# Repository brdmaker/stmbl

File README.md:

CI (`.github/workflows/ci.yml`): the host simulator's `make -C host check` and the firmware build (`make deploy`, vibsensor, brdstepper; the images are kept as artifacts) on every push and pull request.

DISCLAIMER
===

THE AUTHORS OF THIS SOFTWARE ACCEPT ABSOLUTELY NO LIABILITY FOR
ANY HARM OR LOSS RESULTING FROM ITS USE.  IT IS _EXTREMELY_ UNWISE
TO RELY ON SOFTWARE ALONE FOR SAFETY.  Any machinery capable of
harming persons must have provisions for completely removing power
from all motors, etc, before persons enter any danger area.  All
machinery must be designed to comply with local and national safety
codes, and the authors of this software can not, and do not, take
any responsibility for such compliance.

This software is released under the GPLv3.

STMBL
=====
There is work in progress on documentation: https://github.com/rene-dev/stmbl/blob/master/docs/src/Getting%20Started.adoc

**IRC: #stmbl on irc.hackint.eu**
https://webirc.hackint.org/#stmbl

STMBL is an open source servo drive designed for Retrofitting CNC machines and Robots. It supports Industrial AC and DC servos with up to 320V and 2kW (see [specs](https://github.com/rene-dev/stmbl/wiki/specs) for details).

Documentation about the PCB and pinout of the feedback connector:

https://github.com/rene-dev/stmbl/wiki/Pinouts

https://github.com/rene-dev/stmbl/wiki/PCB

##### Hardware version 4.1

##### Driving a Bosch Turboscara
https://www.youtube.com/watch?v=d6NH1W7DUnQ  
https://www.youtube.com/watch?v=oTllxnYAgFc

##### Driving a Manutec Robot
https://www.youtube.com/watch?v=gwgnAeGjZrA  
https://www.youtube.com/watch?v=wXLcAZwjlzE

##### Driving a Weeke BP12 VMC
https://www.youtube.com/watch?v=24LftGNp4MI

##### Driving a Haas VF0 (Spindle + Axes)
https://www.youtube.com/watch?v=kqenepupJIs

##### Drivetest
https://www.youtube.com/watch?v=-E1o_5cFyto

#### Supported Motors
* Synchronous AC Servos
* Asynchronous AC Servos
* DC Servos
* 2 Phase HF spindle motors

#### Supported Feedback systems
* Resolvers
* Incremental encoders
* sin/cos encoder interpolation
* Mitsubishi absolute encoders
* Sanyo Denki absolute encoders
* Yaskawa absolute encoders
* Sick HIPERFACE®
* Tamagawa SmartAbs

##### Planned:
* EnDat
* BiSS
* SSI
* Sanyo Denki wire-saving incremental encoder

#### Supported Position/Velocity Commands Inputs:
* Smartserial
* Quadrature
* Step/direction
* RS485

#### TODO
* Sensorless FOC

#### Directories
* [hw/spice/](hw/spice/) Spice simulation for resolver interface
* [hw/kicad/v4.0/](hw/kicad/v4.0/) kicad files for version 4
* [src/](src/) STM32F4 code, command, feedback and control loop
* [stm32f303/](stm32f303/) STM32F3 code, running on the HV side, generating PWM

##### Commercial Applications

Should you find the GPL license insufficient for your needs, other licenses
can be purchased from my company.

Likewise, please contact us should you wish to fund the further development
of this project, or are interesed in custom hardware, software, or commercial support.

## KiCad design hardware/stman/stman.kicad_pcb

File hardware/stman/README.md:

# stman KiCad project

The schematic of **stman**, the stmbl with an analog output
([docs/stman.md](../../docs/stman.md)). It is stmbl v4.0's LV board
(`hw/kicad/v4.0`) with the stman changes, as a KiCad 7 project. The
schematic is in [doc/stman-schematic.pdf](doc/stman-schematic.pdf).

**stmbl's sheets keep their drawing.** KiCad 7 can't read the KiCad 5
sheets, so `gen/build.py` converts them with `hardware/kigen/legacy.py`.
Every symbol, wire, junction, label and note stays where stmbl has it. Then
it edits them in place.

| sheet | what |
|---|---|
| `stman.kicad_sch` | root, stmbl's `ctrl.sch`: P14 (the HV board link) removed; the new sheets added |
| `supply.kicad_sch` | stmbl's: P3 24 V in (+UI / 0VI), D200 reverse polarity in the wire up from P3, bucks 5 V / 12 V / port 5 V now LMR51420YF (ACT4088 is EOL; stmbl's drawing, pins renumbered, dividers for VFB 0.6 V, EN R212-R214, D9/D12/D13 not fitted, input caps 4.7 µF 50 V; see docs/stman.md, *Power tree*), LDO 3.3 V |
| `f4.kicad_sch` | stmbl's MCU sheet. U22 (ESD on the CMD lines) removed. The MCU pins stman uses carry their new nets as global labels where stmbl's labels were, or at the pin when it was tied to something else (`build.MCU`) |
| `cmd.kicad_sch` | stmbl's CMD port, isolated. U8/U9 stay on the cable side (SS_5V, SS_GND, SS_SHIELD); U10, U11 and their parts are removed; U200 ISO7331FC joins them to the MCU; JP200/JP201 pick the cable's +5 V and GND pairs |
| `fb.kicad_sch` (FB0, FB1) | stmbl's, with a polyfuse (F200 / F201) between the port supply and the connector's pin 7 |
| `io.kicad_sch` | stmbl's IO sheet with the outputs, analog inputs, fan and 2x6 header removed; the status LEDs kept |
| `dac.kicad_sch` | new: AD5761R ×2, OPA2197 Sallen-Key low-pass, TVS, J5; NMA1215 ±15 V |
| `ain.kicad_sch` | new: AD7606 monitor ADC, input resistors, rail dividers, J6 |
| `drvio.kicad_sch` | new: ITS724G ×2 (OUT1-8, J7), 8 inputs (J8), MAX6369 watchdog and the 74LVC2G08 gate on OUT1/OUT2 |

The new sheets are drawn the way `hardware/kigen` draws: parts in framed
groups, each pin joined to its net by a label. Global labels connect them
to the MCU sheet.

Refs from 200 up are stman's. The others are stmbl v4.0's, with the same
values and footprints (stmbl's footprint library, `fp-lib-table` ->
`hw/kicad/lib/stmbl.pretty`).

## The board

`stman.kicad_pcb` comes from `gen/pcb.py`. It is placed, not routed; see
docs/stman.md, *The board*.
- **Outline:** stmbl v4.0's (the v4 case fits), with the HV/LV slots
  removed.
- **stmbl's parts:** each is stmbl's footprint, copied from
  `hw/kicad/v4.0/stmbl_4.0.kicad_pcb` where stmbl placed it.
- **New parts:** the connectors and main ICs at fixed positions (`FIXED`,
  `FLUSH`); their passives beside the parts they connect to.
- **Isolation barrier:** a copper-free rule area for the smart-serial cable
  side.
- **Ground plane:** on In1, not filled.

`gen/pcb.py` prints the courtyard overlaps that involve new parts (none),
and how many stmbl v4.0 has among its own parts (20, unchanged).

## Make

| target | does |
|---|---|
| `make sch` | `gen/build.py`: convert, edit, add the new sheets |
| `make check` | `gen/check.py`: the netlist kicad-cli exports against two references (below) |
| `make pcb` | `gen/pcb.py`: the board (placement redone; hand edits to it are lost) |
| `make doc` | the PDF and the placement renders |

`gen/check.py` checks:
- **stmbl's own nets:** every net of stmbl's 2018 netlist
  (`hw/kicad/v4.0/stmbl_4.0.net`) among the parts kept is still one net,
  except the ones stman changes on purpose;
- **stman's nets:** every pin of the new parts, the MCU pins and the
  isolator is on the net the design gives it, and no two of those nets are
  joined.

At the time of writing it reports 229 nets, 338 parts, OK.

Edit the generator (`gen/build.py`, `gen/newsheets.py`) rather than the
sheets while the design is moving. Once layout starts, edit in KiCad.

## To check before layout (✱)

- **AD5761R:** the pin numbers (its symbol is drawn from the datasheet's pin
  names).
- **AD7606:** in serial mode, check that DOUT_A is tri-stated with /CS high
  (it shares MISO with the DACs).
- **MAX6369:** the SET0-2 timeout table.
- **ITS724G:** the status logic.
- **Mesa's smart-serial RJ45 pinout:** which pairs carry +5 V and GND
  (JP200/JP201).

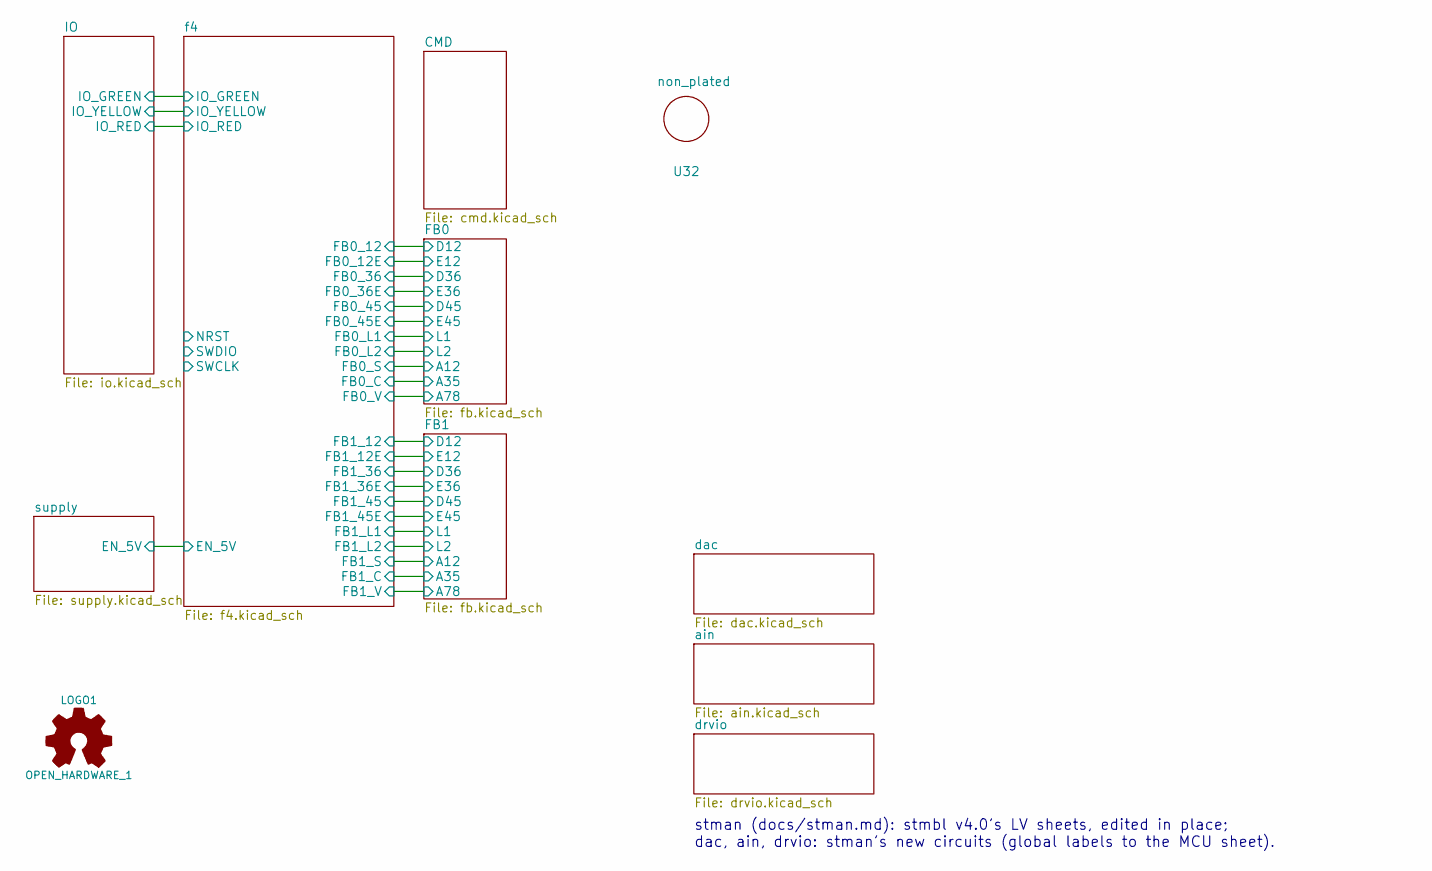
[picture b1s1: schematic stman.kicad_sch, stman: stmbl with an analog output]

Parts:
LOGO1: OPEN_HARDWARE_1; Symbol_OSHW-Logo_SilkScreen
U32: non_plated; non_plated_3mm

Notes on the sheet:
stman (docs/stman.md): stmbl v4.0's LV sheets, edited in place; dac, ain, drvio: stman's new circuits (global labels to the MCU sheet).

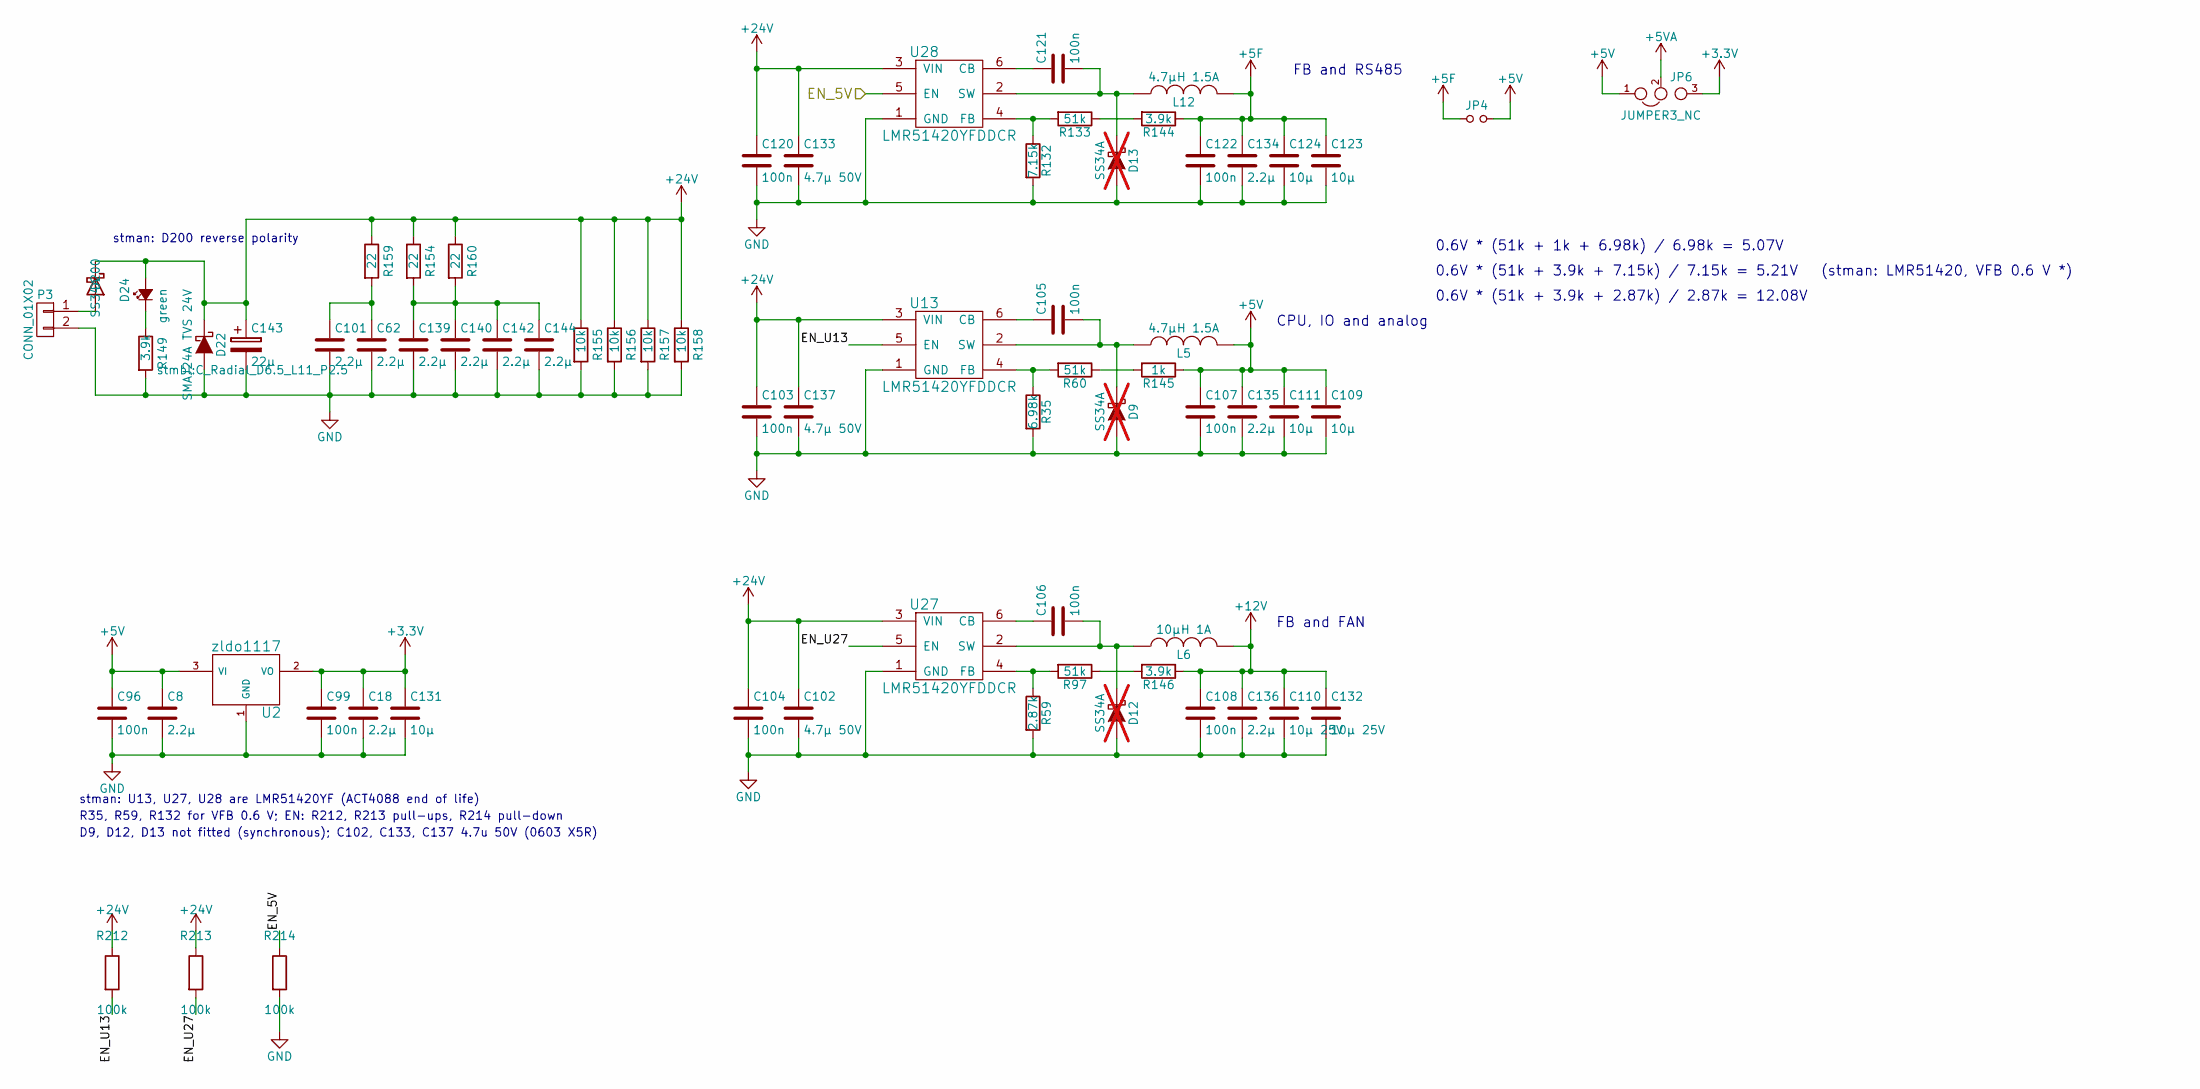
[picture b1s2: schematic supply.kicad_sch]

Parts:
C8, C18, C62, C101, C134, C135, C136, C139, C140, C142, C144: 2.2µ; C_0603; Voltage 35V; Tolerance X5R
C96, C99, C103, C104, C105, C106, C107, C108, C120, C121, C122: 100n; C_0603; Voltage 50V; Tolerance X5R
C102, C133, C137: 4.7µ 50V; C_0603; Voltage 35V; Tolerance X5R
C109, C111, C123, C124, C131: 10µ; C_0805; Voltage 25V; Tolerance X5R
C110, C132: 10µ 25V; C_0805; Voltage 25V; Tolerance X5R
C143: 22µ; C_Radial_D6.5_L11_P2.5; Voltage 50V
D9, D12, D13: SS34A; SMA_Standard; not fitted
D22: SMAJ24A TVS 24V; SMA_Standard
D24: green; LED-0805-SIDE
D200: SS34A; SMA_Standard
JP4: Jumper_NO_Small; SOLDER_JUMPER
JP6: JUMPER3_NC; SOLDER_JUMPER_3_NC
L5, L12: 4.7µH 1.5A; SMD_INDUCTOR_32x25
L6: 10µH 1A; SMD_INDUCTOR_32x25
P3: CONN_01X02; RM3.5_1x2
R35: 6.98k; R_0603; Tolerance 1%
R59: 2.87k; R_0603; Tolerance 1%
R60, R97, R133: 51k; R_0603; Tolerance 1%
R132: 7.15k; R_0603; Tolerance 1%
R144, R146, R149: 3.9k; R_0603; Tolerance 1%
R145: 1k; R_0603; Tolerance 1%
R154, R159, R160: 22; R_0603; Tolerance 1%
R155, R156, R157, R158: 10k; R_0603; Tolerance 1%
R212, R213, R214: 100k; R_0603
U2: zldo1117; SOT-223
U13, U27, U28: LMR51420YFDDCR; SOT-23-6

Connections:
+5F: C122.1, C123.1, C124.1, C134.1, JP4.1, L12.2, R144.1; also elsewhere on the board
+5V: C8.1, C96.1, C107.1, C109.1, C111.1, C135.1, JP4.2, JP6.1, L5.2, R145.1, U2.3 (VI); also elsewhere on the board
+5VA: JP6.2; also elsewhere on the board
+12V: C108.1, C110.1, C132.1, C136.1, L6.2, R146.1; also elsewhere on the board
+24V: C102.1, C103.1, C104.1, C120.1, C133.1, C137.1, C143.1, D22.1 (K), D24.2 (A), D200.1 (K), R154.1, R155.1, R156.1, R157.1, R158.1, R159.1, R160.1, R212.1, R213.1, U13.3 (VIN), U27.3 (VIN), U28.3 (VIN); also elsewhere on the board
/supply/EN_5V: R214.1, U28.5 (EN); also elsewhere on the board
/supply/EN_U13: R212.2, U13.5 (EN)
/supply/EN_U27: R213.2, U27.5 (EN)
GND: C8.2, C18.2, C62.2, C96.2, C99.2, C101.2, C102.2, C103.2, C104.2, C107.2, C108.2, C109.2, C110.2, C111.2, C120.2, C122.2, C123.2, C124.2, C131.2, C132.2, C133.2, C134.2, C135.2, C136.2, C137.2, C139.2, C140.2, C142.2, C143.2, C144.2, D9.2 (A), D12.2 (A), D13.2 (A), D22.2 (A), P3.2, R35.2, R59.2, R132.2, R149.2, R155.2, R156.2, R157.2, R158.2, R214.2, U2.1 (GND), U13.1 (GND), U27.1 (GND), U28.1 (GND); also elsewhere on the board
unnamed: C62.1, C101.1, R159.2
unnamed: C139.1, C140.1, C142.1, C144.1, R154.2, R160.2
unnamed: C105.2, D9.1 (K), L5.1, U13.2 (SW)
unnamed: C106.2, D12.1 (K), L6.1, U27.2 (SW)
unnamed: C121.2, D13.1 (K), L12.1, U28.2 (SW)
unnamed: D24.1 (K), R149.1
unnamed: D200.2 (A), P3.1
unnamed: R133.1, R144.2
unnamed: R60.1, R145.2
unnamed: R97.1, R146.2
unnamed: C105.1, U13.6 (CB)
unnamed: R35.1, R60.2, U13.4 (FB)
unnamed: C106.1, U27.6 (CB)
unnamed: R59.1, R97.2, U27.4 (FB)
unnamed: C121.1, U28.6 (CB)
unnamed: R132.1, R133.2, U28.4 (FB)

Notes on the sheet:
FB and FAN
CPU, IO and analog
FB and RS485
0.6V * (51k + 3.9k + 7.15k) / 7.15k = 5.21V (stman: LMR51420, VFB 0.6 V *)
0.6V * (51k + 3.9k + 2.87k) / 2.87k = 12.08V
0.6V * (51k + 1k + 6.98k) / 6.98k = 5.07V
stman: D200 reverse polarity
stman: U13, U27, U28 are LMR51420YF (ACT4088 end of life)
R35, R59, R132 for VFB 0.6 V; EN: R212, R213 pull-ups, R214 pull-down
D9, D12, D13 not fitted (synchronous); C102, C133, C137 4.7u 50V (0603 X5R)

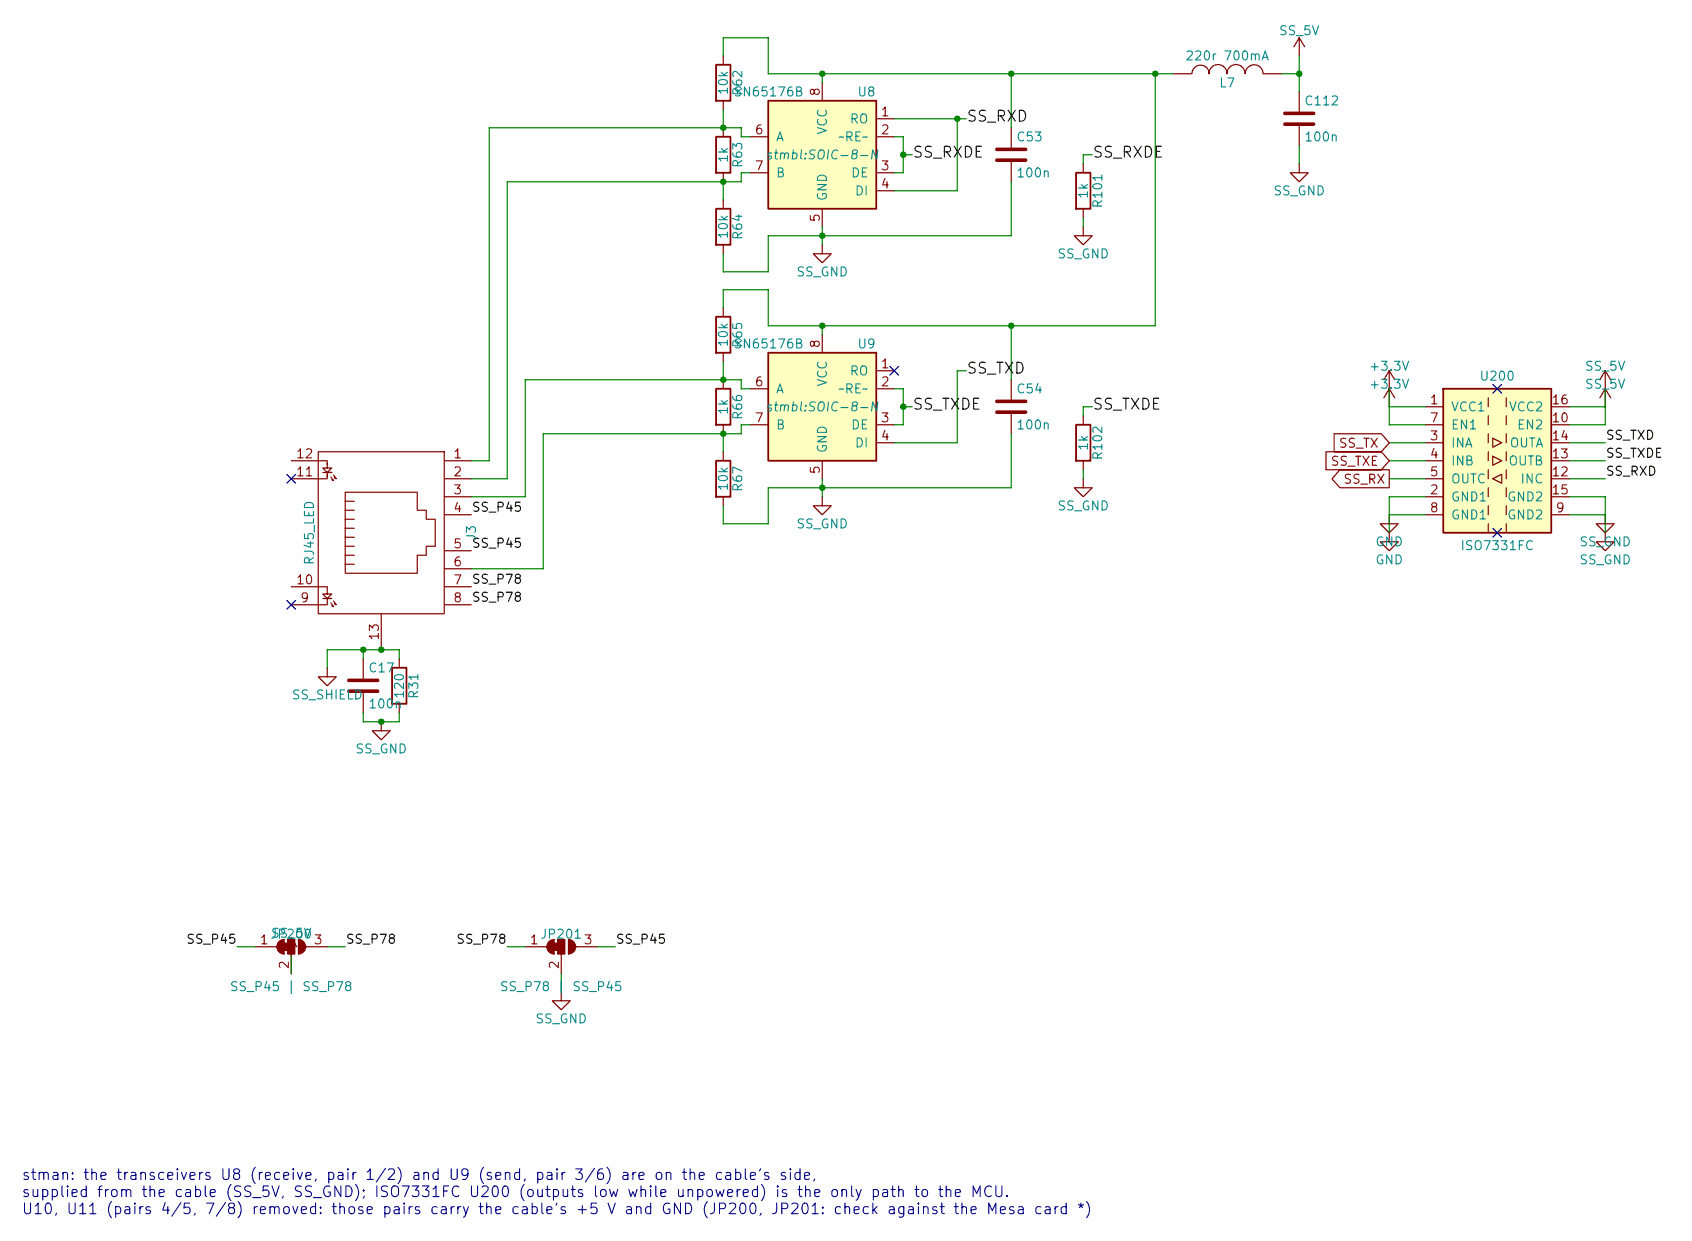
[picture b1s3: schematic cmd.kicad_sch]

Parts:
C17, C53, C54, C112: 100n; C_0603; Tolerance X5R; Voltage 50V
J3: RJ45_LED
JP200: SS_P45 | SS_P78; SolderJumper-3_P1.3mm_Bridged12_RoundedPad1.0x1.5mm
JP201: SS_P78 | SS_P45; SolderJumper-3_P1.3mm_Bridged12_RoundedPad1.0x1.5mm
L7: 220r 700mA; R_0603
R31: 120; R_0603; Tolerance 1%
R62, R64, R65, R67: 10k; R_0603; Tolerance 1%
R63, R66, R101, R102: 1k; R_0603; Tolerance 1%
U8, U9: SN65176B; SOIC-8-N
U200: ISO7331FC; SOIC-16W_7.5x10.3mm_P1.27mm

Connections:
/CMD/SS_P45: J3.4, J3.5, JP200.1 (A), JP201.3 (B)
/CMD/SS_P78: J3.7, J3.8, JP200.3 (B), JP201.1 (A)
/CMD/SS_RXD: U8.1 (RO), U8.4 (DI), U200.12 (INC)
/CMD/SS_RXDE: R101.1, U8.2 (~RE~), U8.3 (DE)
/CMD/SS_TXD: U9.4 (DI), U200.14 (OUTA)
/CMD/SS_TXDE: R102.1, U9.2 (~RE~), U9.3 (DE), U200.13 (OUTB)
GND: U200.2 (GND1), U200.8 (GND1); also elsewhere on the board
unnamed: J3.1, R62.2, R63.1, U8.6 (A)
unnamed: J3.2, R63.2, R64.1, U8.7 (B)
unnamed: C53.1, C54.1, L7.1, R62.1, R65.1, U8.8 (VCC), U9.8 (VCC)
unnamed: J3.3, R65.2, R66.1, U9.6 (A)
unnamed: J3.6, R66.2, R67.1, U9.7 (B)
SS_5V: C112.1, JP200.2 (C), L7.2, U200.10 (EN2), U200.16 (VCC2)
SS_GND: C17.2, C53.2, C54.2, C112.2, JP201.2 (C), R31.2, R64.2, R67.2, R101.2, R102.2, U8.5 (GND), U9.5 (GND), U200.9 (GND2), U200.15 (GND2)
SS_RX: U200.5 (OUTC); also elsewhere on the board
SS_SHIELD: C17.1, J3.13, R31.1
SS_TX: U200.3 (INA); also elsewhere on the board
SS_TXE: U200.4 (INB); also elsewhere on the board

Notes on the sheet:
stman: the transceivers U8 (receive, pair 1/2) and U9 (send, pair 3/6) are on the cable's side, supplied from the cable (SS_5V, SS_GND); ISO7331FC U200 (outputs low while unpowered) is the only path to the MCU. U10, U11 (pairs 4/5, 7/8) removed: those pairs carry the cable's +5 V and GND (JP200, JP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

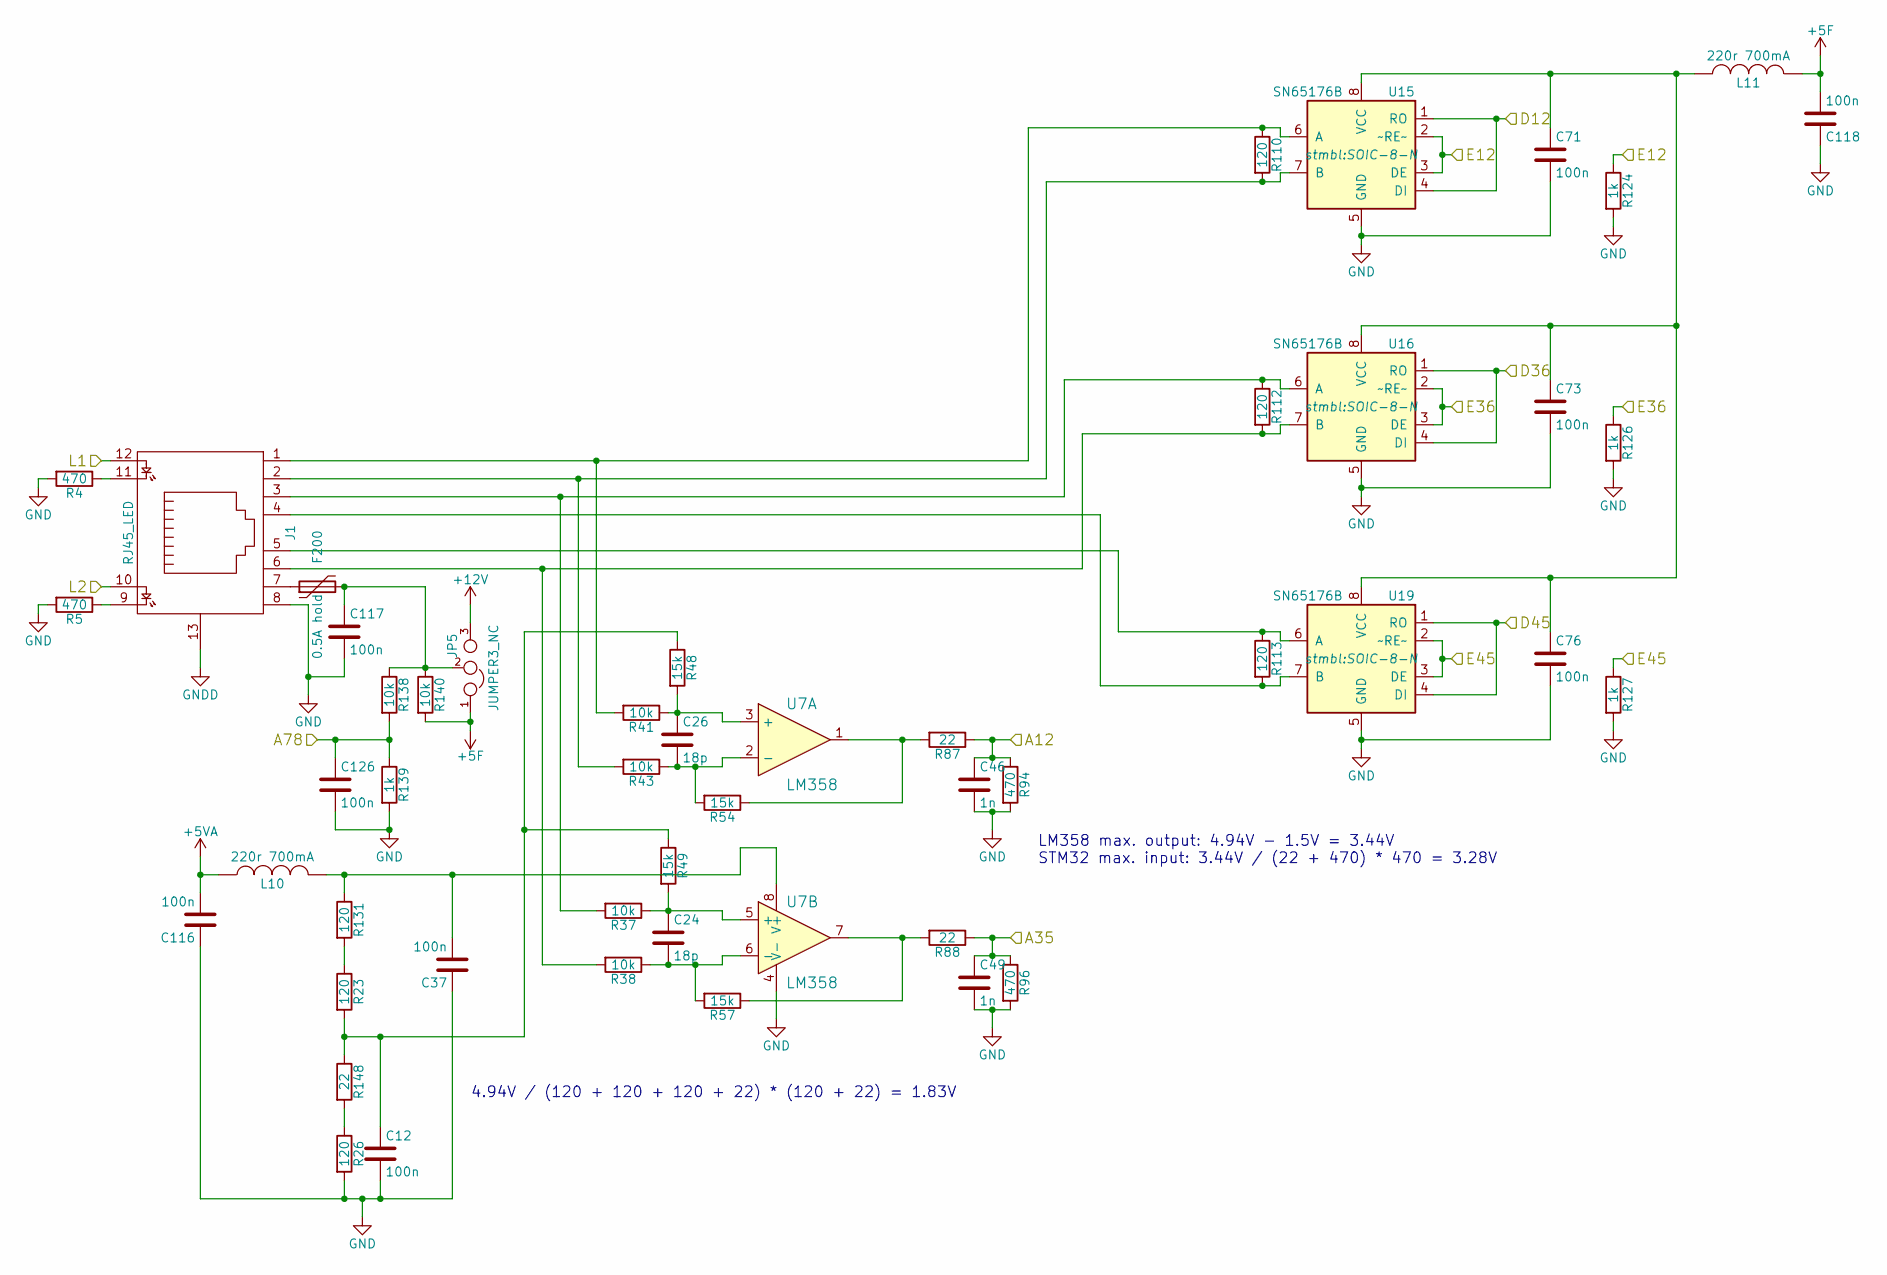
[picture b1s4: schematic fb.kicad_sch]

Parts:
C12, C37, C71, C73, C76, C116, C117, C118, C126: 100n; C_0603; Voltage 50V; Tolerance X5R
C24, C26: 18p; C_0603; Voltage 50V; Tolerance X5R
C46, C49: 1n; C_0603; Voltage 50V; Tolerance X5R
F200: 0.5A hold; Fuse_1206_3216Metric
J1: RJ45_LED
JP5: JUMPER3_NC; SOLDER_JUMPER_3_NC
L10, L11: 220r 700mA; R_0603
R4, R5, R94, R96: 470; R_0603; Tolerance 1%
R23, R26, R110, R112, R113, R131: 120; R_0603; Tolerance 1%
R37, R38, R41, R43, R138, R140: 10k; R_0603; Tolerance 1%
R48, R49, R54, R57: 15k; R_0603; Tolerance 1%
R87, R88, R148: 22; R_0603; Tolerance 1%
R124, R126, R127, R139: 1k; R_0603; Tolerance 1%
U7: LM358; SOIC-8-N
U15, U16, U19: SN65176B; SOIC-8-N

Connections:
+5F: C118.2, JP5.1, L11.1, R140.2; also elsewhere on the board
+5VA: C116.2, L10.1; also elsewhere on the board
+12V: JP5.3; also elsewhere on the board
/FB1/A12: C46.1, R87.1, R94.1; also elsewhere on the board
/FB1/A35: C49.1, R88.1, R96.1; also elsewhere on the board
/FB1/A78: C126.1, R138.2, R139.1; also elsewhere on the board
/FB1/D12: U15.1 (RO), U15.4 (DI); also elsewhere on the board
/FB1/D36: U16.1 (RO), U16.4 (DI); also elsewhere on the board
/FB1/D45: U19.1 (RO), U19.4 (DI); also elsewhere on the board
/FB1/E12: R124.1, U15.2 (~RE~), U15.3 (DE); also elsewhere on the board
/FB1/E36: R126.1, U16.2 (~RE~), U16.3 (DE); also elsewhere on the board
/FB1/E45: R127.1, U19.2 (~RE~), U19.3 (DE); also elsewhere on the board
/FB1/L1: J1.12; also elsewhere on the board
/FB1/L2: J1.10; also elsewhere on the board
GND: C12.2, C37.1, C46.2, C49.2, C71.2, C73.2, C76.2, C116.1, C117.2, C118.1, C126.2, J1.8, R4.2, R5.2, R26.2, R94.2, R96.2, R124.2, R126.2, R127.2, R139.2, U7.4 (V-), U15.5 (GND), U16.5 (GND), U19.5 (GND); also elsewhere on the board
GNDD: J1.13; also elsewhere on the board
unnamed: C12.1, R23.2, R48.1, R49.1, R148.1
unnamed: J1.9, R5.1
unnamed: J1.11, R4.1
unnamed: R54.1, R87.2, U7.1
unnamed: R57.1, R88.2, U7.7
unnamed: R23.1, R131.2
unnamed: R26.1, R148.2
unnamed: C26.1, R41.1, R48.2, U7.3 (+)
unnamed: C26.2, R43.1, R54.2, U7.2 (-)
unnamed: C24.1, R37.1, R49.2, U7.5 (+)
unnamed: C24.2, R38.1, R57.2, U7.6 (-)
unnamed: C37.2, L10.2, R131.1, U7.8 (V+)
unnamed: J1.1, R41.2, R110.1, U15.6 (A)
unnamed: J1.2, R43.2, R110.2, U15.7 (B)
unnamed: C71.1, C73.1, C76.1, L11.2, U15.8 (VCC), U16.8 (VCC), U19.8 (VCC)
unnamed: J1.3, R37.2, R112.1, U16.6 (A)
unnamed: J1.6, R38.2, R112.2, U16.7 (B)
unnamed: J1.5, R113.1, U19.6 (A)
unnamed: J1.4, R113.2, U19.7 (B)

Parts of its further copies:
C13, C36, C72, C74, C75, C113, C114, C115, C125: 100n; C_0603; Voltage 50V; Tolerance X5R
C25, C27: 18p; C_0603; Voltage 50V; Tolerance X5R
C47, C48: 1n; C_0603; Voltage 50V; Tolerance X5R
F201: 0.5A hold; Fuse_1206_3216Metric
J2: RJ45_LED
JP2: JUMPER3_NC; SOLDER_JUMPER_3_NC
L8, L9: 220r 700mA; R_0603
R3, R6, R93, R95: 470; R_0603; Tolerance 1%
R24, R25, R109, R111, R114, R130: 120; R_0603; Tolerance 1%
R36, R39, R42, R44, R135, R137: 10k; R_0603; Tolerance 1%
R47, R50, R55, R56: 15k; R_0603; Tolerance 1%
R86, R89, R147: 22; R_0603; Tolerance 1%
R123, R125, R128, R136: 1k; R_0603; Tolerance 1%
U6: LM358; SOIC-8-N
U14, U17, U18: SN65176B; SOIC-8-N

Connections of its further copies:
+5F: C115.2, JP2.1, L9.1, R137.2; also elsewhere on the board
+5VA: C113.2, L8.1; also elsewhere on the board
+12V: JP2.3; also elsewhere on the board
/FB0/A12: C47.1, R86.1, R93.1; also elsewhere on the board
/FB0/A35: C48.1, R89.1, R95.1; also elsewhere on the board
/FB0/A78: C125.1, R135.2, R136.1; also elsewhere on the board
/FB0/D12: U14.1 (RO), U14.4 (DI); also elsewhere on the board
/FB0/D36: U17.1 (RO), U17.4 (DI); also elsewhere on the board
/FB0/D45: U18.1 (RO), U18.4 (DI); also elsewhere on the board
/FB0/E12: R123.1, U14.2 (~RE~), U14.3 (DE); also elsewhere on the board
/FB0/E36: R125.1, U17.2 (~RE~), U17.3 (DE); also elsewhere on the board
/FB0/E45: R128.1, U18.2 (~RE~), U18.3 (DE); also elsewhere on the board
/FB0/L1: J2.12; also elsewhere on the board
/FB0/L2: J2.10; also elsewhere on the board
GND: C13.2, C36.1, C47.2, C48.2, C72.2, C74.2, C75.2, C113.1, C114.2, C115.1, C125.2, J2.8, R3.2, R6.2, R25.2, R93.2, R95.2, R123.2, R125.2, R128.2, R136.2, U6.4 (V-), U14.5 (GND), U17.5 (GND), U18.5 (GND); also elsewhere on the board
GNDD: J2.13; also elsewhere on the board
unnamed: C13.1, R24.2, R47.1, R50.1, R147.1
unnamed: J2.9, R6.1
unnamed: J2.11, R3.1
unnamed: R55.1, R86.2, U6.1
unnamed: R56.1, R89.2, U6.7
unnamed: R24.1, R130.2
unnamed: R25.1, R147.2
unnamed: C27.1, R42.1, R47.2, U6.3 (+)
unnamed: C27.2, R44.1, R55.2, U6.2 (-)
unnamed: C25.1, R36.1, R50.2, U6.5 (+)
unnamed: C25.2, R39.1, R56.2, U6.6 (-)
unnamed: C36.2, L8.2, R130.1, U6.8 (V+)
unnamed: J2.1, R42.2, R109.1, U14.6 (A)
unnamed: J2.2, R44.2, R109.2, U14.7 (B)
unnamed: C72.1, C74.1, C75.1, L9.2, U14.8 (VCC), U17.8 (VCC), U18.8 (VCC)
unnamed: J2.3, R36.2, R111.1, U17.6 (A)
unnamed: J2.6, R39.2, R111.2, U17.7 (B)
unnamed: J2.5, R114.1, U18.6 (A)
unnamed: J2.4, R114.2, U18.7 (B)

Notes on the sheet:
LM358 max. output: 4.94V - 1.5V = 3.44V STM32 max. input: 3.44V / (22 + 470) * 470 = 3.28V
4.94V / (120 + 120 + 120 + 22) * (120 + 22) = 1.83V

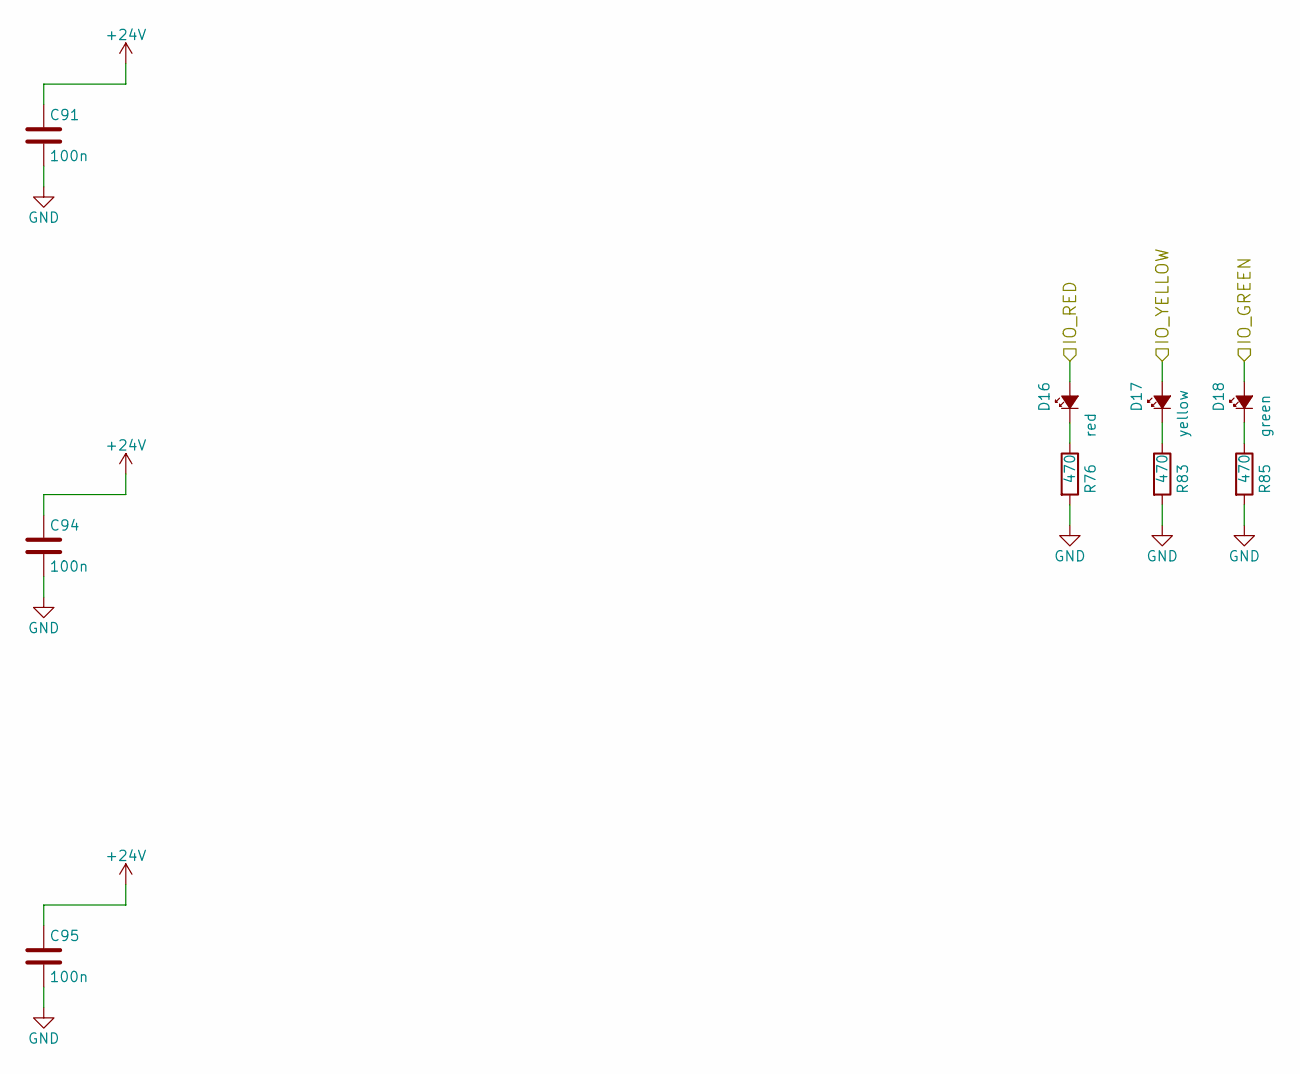
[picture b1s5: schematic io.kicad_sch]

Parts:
C91, C94, C95: 100n; C_0603; Voltage 50V; Tolerance X5R
D16: red; LED-0805-SIDE
D17: yellow; LED-0805-SIDE
D18: green; LED-0805-SIDE
R76, R83, R85: 470; R_0603; Tolerance 1%

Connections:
+24V: C91.1, C94.1, C95.1; also elsewhere on the board
/IO/IO_GREEN: D18.2 (A); also elsewhere on the board
/IO/IO_RED: D16.2 (A); also elsewhere on the board
/IO/IO_YELLOW: D17.2 (A); also elsewhere on the board
GND: C91.2, C94.2, C95.2, R76.2, R83.2, R85.2; also elsewhere on the board
unnamed: D16.1 (K), R76.1
unnamed: D17.1 (K), R83.1
unnamed: D18.1 (K), R85.1

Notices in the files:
stm32f303/src/main.c:
Copyright (C) 2013-2017 Rene Hopf <renehopf@mac.com>
Copyright (C) 2013-2017 Nico Stute <crinq@crinq.de>
This program is free software: you can redistribute it and/or modify
it under the terms of the GNU General Public License as published by
the Free Software Foundation, either version 3 of the License, or
(at your option) any later version.
